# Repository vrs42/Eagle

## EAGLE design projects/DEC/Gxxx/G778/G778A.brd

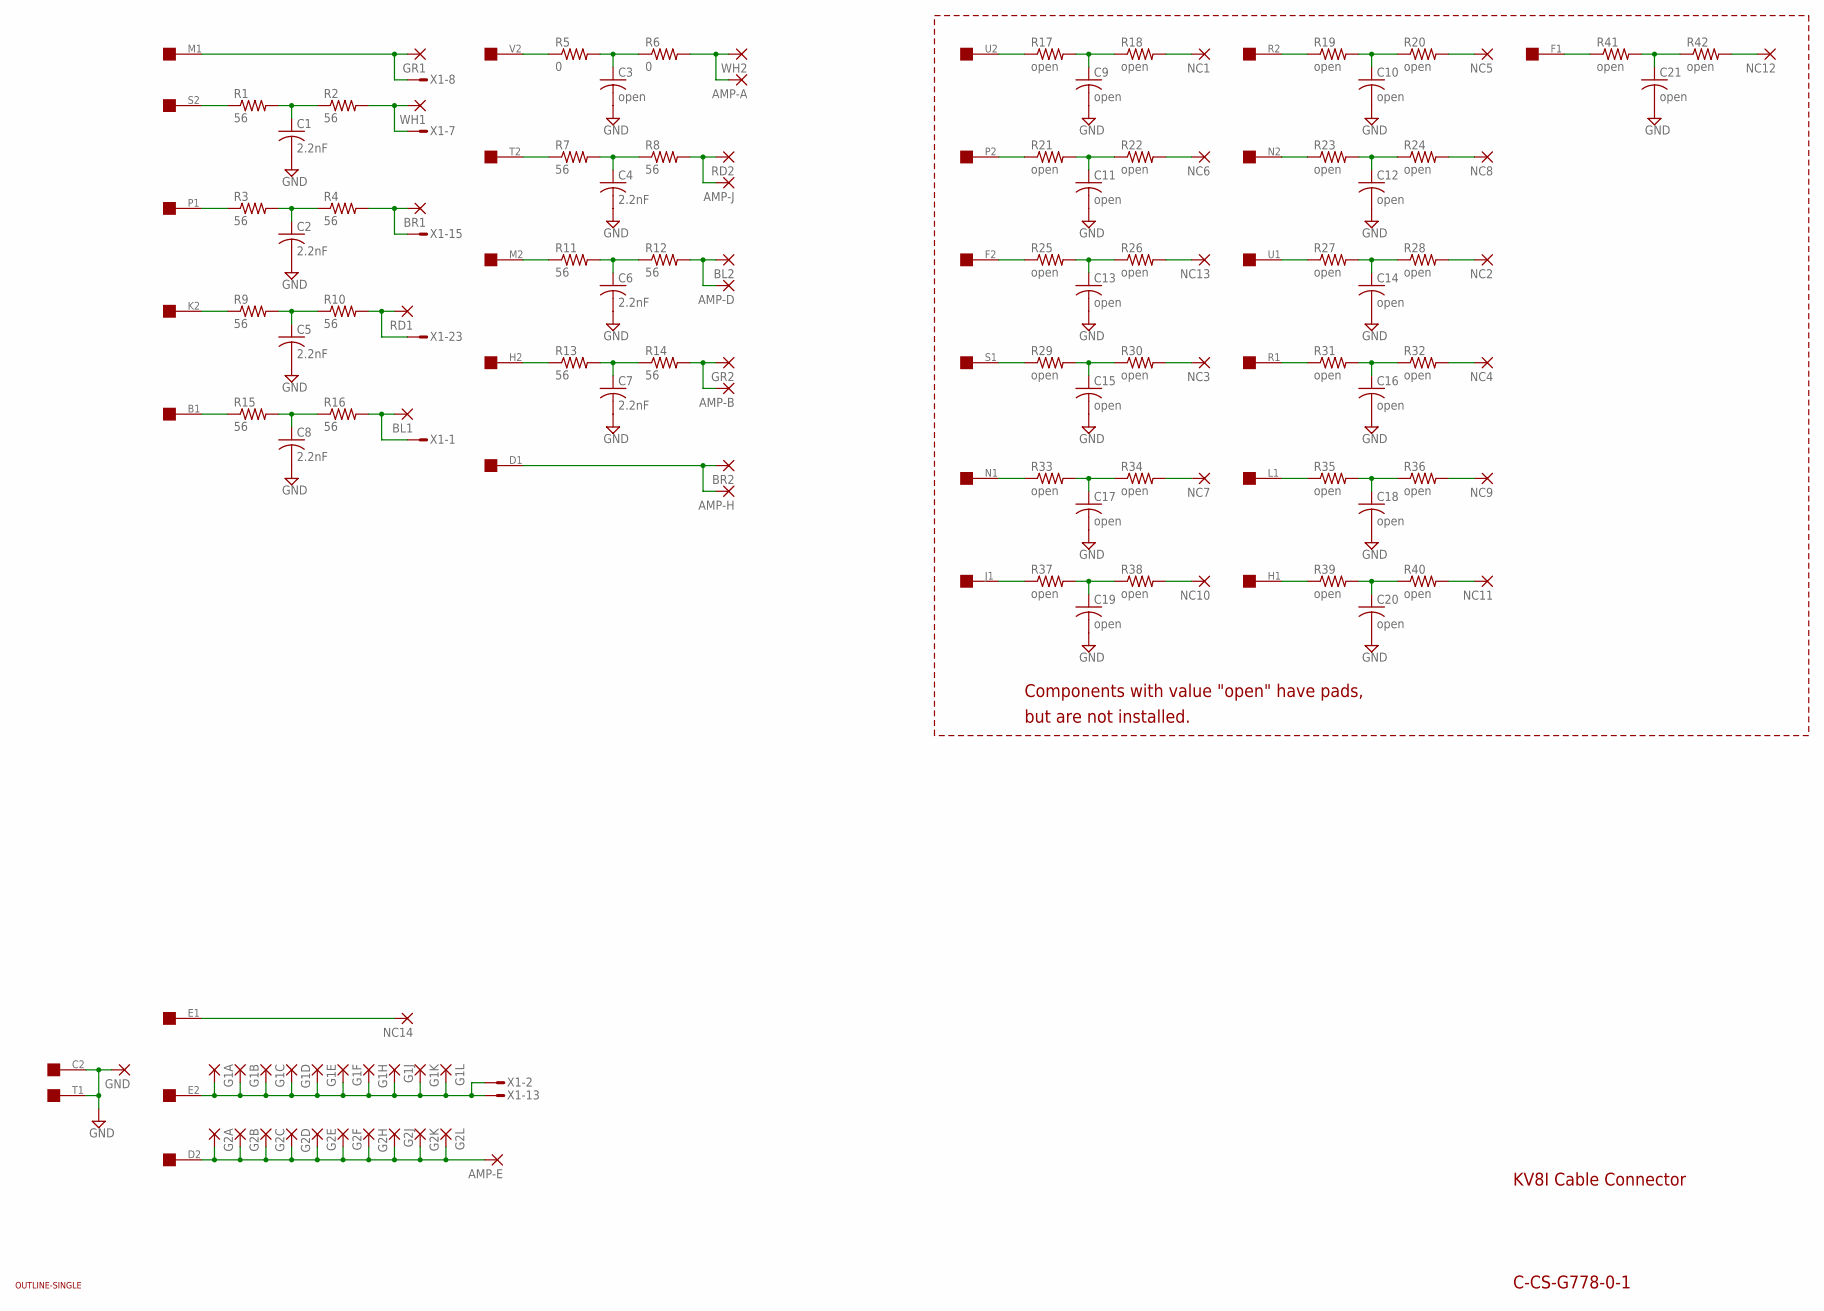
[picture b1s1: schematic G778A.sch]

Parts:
AMP-A: 2,54/1,0
AMP-B: 2,54/1,0
AMP-D: 2,54/1,0
AMP-E: 2,54/1,0
AMP-H: 2,54/1,0
AMP-J: 2,54/1,0
BL1, BL2: 2,54/1,0
BR1, BR2: 2,54/1,0
C1, C2, C4, C5, C6, C7, C8: 2.2nF; C102-043X133
C3, C9, C10, C11, C12, C13, C14, C15, C16, C17, C18, C19, C20, C21: open; C102-043X133
G1A, G1B, G1C, G1D, G1E, G1F, G1H, G1J, G1K, G1L, G2A, G2B, G2C, G2D, G2E, G2F, G2H, G2J, G2K, G2L: 2,54/1,0
GND: 2,54/1,0
GR1, GR2: 2,54/1,0
NC1, NC2, NC3, NC4, NC5, NC6, NC7, NC8, NC9, NC10, NC11, NC12, NC13, NC14: 2,54/1,0
R1, R2, R3, R4, R7, R8, R9, R10, R11, R12, R13, R14, R15, R16: 56; 0207/10
R5, R6: 0; 0207/10
R17, R18, R19, R20, R21, R22, R23, R24, R25, R26, R27, R28, R29, R30, R31, R32, R33, R34, R35, R36, R37, R38, R39, R40, R41, R42: open; 0207/10
RD1, RD2: 2,54/1,0
U$1: SINGLE; EDGE-CON2
U$2: OUTLINE-SINGLE; SINGLE
WH1, WH2: 2,54/1,0
X1: M25VS; M25V

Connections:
GND: C1.2, C2.2, C3.2, C4.2, C5.2, C6.2, C7.2, C8.2, C9.2, C10.2, C11.2, C12.2, C13.2, C14.2, C15.2, C16.2, C17.2, C18.2, C19.2, C20.2, C21.2, GND.1, U$1.C2, U$1.T1
unnamed: C1.1, R1.2, R2.1
unnamed: R1.1, U$1.S2
unnamed: R2.2, WH1.1, X1.7
unnamed: C2.1, R3.2, R4.1
unnamed: R3.1, U$1.P1
unnamed: BR1.1, R4.2, X1.15
unnamed: GR1.1, U$1.M1, X1.8
unnamed: G1A.1, G1B.1, G1C.1, G1D.1, G1E.1, G1F.1, G1H.1, G1J.1, G1K.1, G1L.1, U$1.E2, X1.2, X1.13
unnamed: AMP-E.1, G2A.1, G2B.1, G2C.1, G2D.1, G2E.1, G2F.1, G2H.1, G2J.1, G2K.1, G2L.1, U$1.D2
unnamed: C3.1, R5.2, R6.1
unnamed: R5.1, U$1.V2
unnamed: AMP-A.1, R6.2, WH2.1
unnamed: C4.1, R7.2, R8.1
unnamed: R7.1, U$1.T2
unnamed: AMP-J.1, R8.2, RD2.1
unnamed: C5.1, R9.2, R10.1
unnamed: R9.1, U$1.K2
unnamed: R10.2, RD1.1, X1.23
unnamed: C6.1, R11.2, R12.1
unnamed: R11.1, U$1.M2
unnamed: AMP-D.1, BL2.1, R12.2
unnamed: C7.1, R13.2, R14.1
unnamed: R13.1, U$1.H2
unnamed: AMP-B.1, GR2.1, R14.2
unnamed: C8.1, R15.2, R16.1
unnamed: R15.1, U$1.B1
unnamed: BL1.1, R16.2, X1.1
unnamed: C9.1, R17.2, R18.1
unnamed: R17.1, U$1.U2
unnamed: NC1.1, R18.2
unnamed: C10.1, R19.2, R20.1
unnamed: R19.1, U$1.R2
unnamed: NC5.1, R20.2
unnamed: C11.1, R21.2, R22.1
unnamed: R21.1, U$1.P2
unnamed: NC6.1, R22.2
unnamed: C12.1, R23.2, R24.1
unnamed: R23.1, U$1.N2
unnamed: NC8.1, R24.2
unnamed: C13.1, R25.2, R26.1
unnamed: R25.1, U$1.F2
unnamed: NC13.1, R26.2
unnamed: C14.1, R27.2, R28.1
unnamed: R27.1, U$1.U1
unnamed: NC2.1, R28.2
unnamed: C15.1, R29.2, R30.1
unnamed: R29.1, U$1.S1
unnamed: NC3.1, R30.2
unnamed: C16.1, R31.2, R32.1
unnamed: R31.1, U$1.R1
unnamed: NC4.1, R32.2
unnamed: C17.1, R33.2, R34.1
unnamed: R33.1, U$1.N1
unnamed: NC7.1, R34.2
unnamed: C18.1, R35.2, R36.1
unnamed: R35.1, U$1.L1
unnamed: NC9.1, R36.2
unnamed: C19.1, R37.2, R38.1
unnamed: R37.1, U$1.J1
unnamed: NC10.1, R38.2
unnamed: C20.1, R39.2, R40.1
unnamed: R39.1, U$1.H1
unnamed: NC11.1, R40.2
unnamed: C21.1, R41.2, R42.1
unnamed: R41.1, U$1.F1
unnamed: NC12.1, R42.2
unnamed: AMP-H.1, BR2.1, U$1.D1
unnamed: NC14.1, U$1.E1

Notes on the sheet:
KV8I Cable Connector
C-CS-G778-0-1
Components with value "open" have pads,
but are not installed.

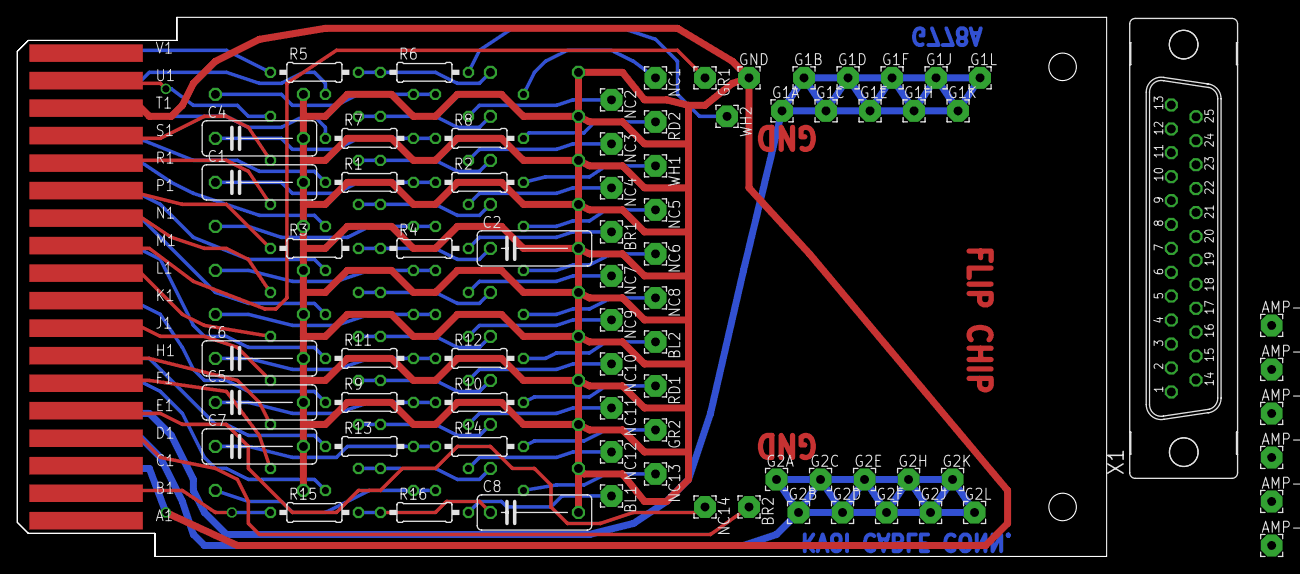
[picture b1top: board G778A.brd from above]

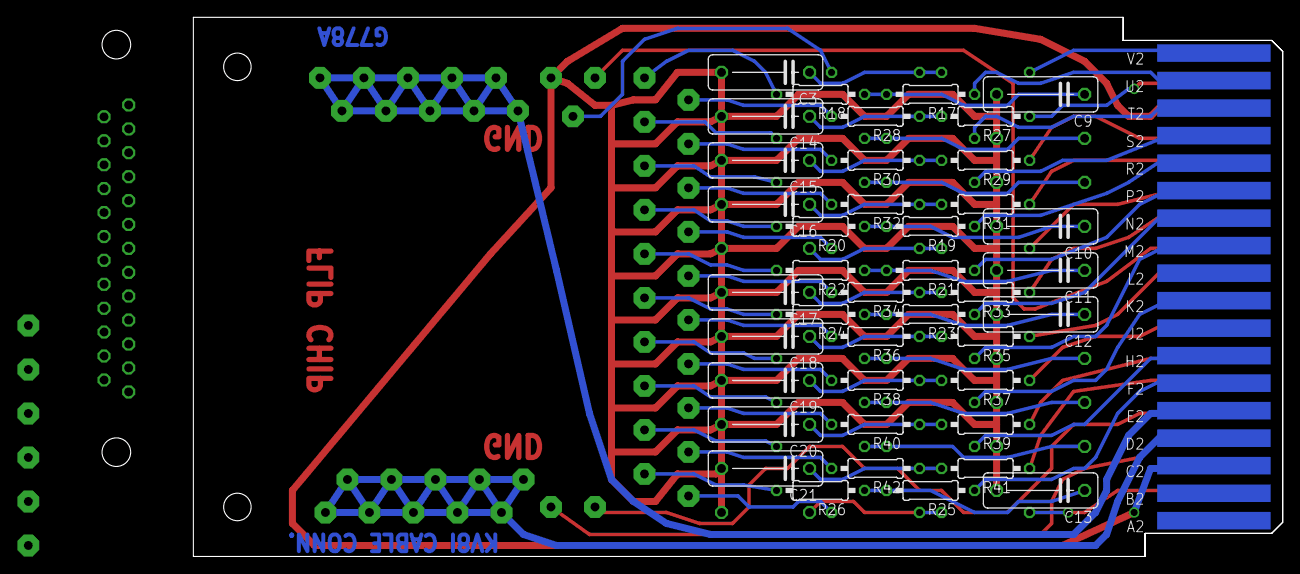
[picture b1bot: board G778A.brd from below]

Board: 2 copper layers, 125.7 x 62.2 mm, 117 parts (40 on the bottom side), 69 nets.

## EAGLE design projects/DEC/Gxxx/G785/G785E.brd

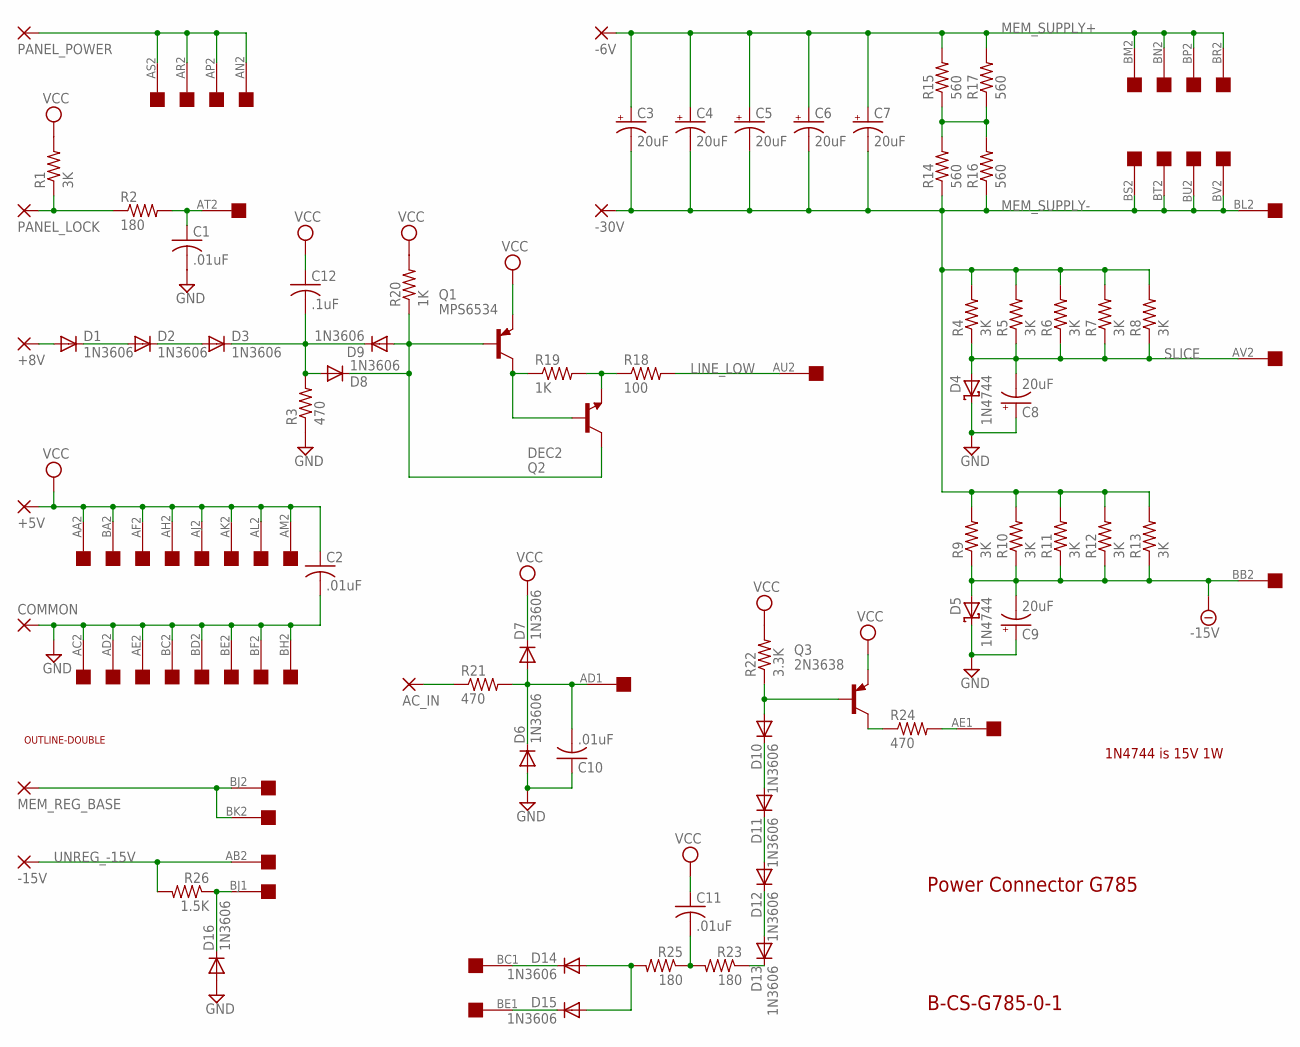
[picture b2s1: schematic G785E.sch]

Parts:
+5V, +8V: 3,81/1,4
-6V, -15V, -30V: 3,81/1,4
AC_IN: 3,81/1,4
C1, C2, C10, C11: .01uF; C050-025X075
C3, C4, C5, C6, C7, C8, C9: 20uF; E25-9
C12: .1uF; C102-043X133
COMMON: 3,81/1,4
D1, D2, D3, D6, D7, D8, D9, D10, D11, D12, D13, D14, D15, D16: 1N3606; DO35-10
D4, D5: 1N4744; DO35-10
MEM_REG_BASE: 3,81/1,4
PANEL_LOCK: 3,81/1,4
PANEL_POWER: 3,81/1,4
Q1: MPS6534; TO39
Q2: DEC2; TO5
Q3: 2N3638; TO39
R1, R4, R5, R6, R7, R8, R9, R10, R11, R12, R13: 3K; 0207/10
R2, R23, R25: 180; 0207/10
R3, R21, R24: 470; 0207/10
R14, R15, R16, R17: 560; 0207/10
R18: 100; 0207/10
R19, R20: 1K; 0207/10
R22: 3.3K; 0207/10
R26: 1.5K; 0207/10
U$1: DOUBLE; EDGE-CON4
U$2: OUTLINE-DOUBLE; DOUBLE

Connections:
-15V: C9.-, D5.A, R9.1, R10.1, R11.1, R12.1, R13.1, U$1.BB2
GND: C1.2, C2.2, C8.+, C9.+, C10.1, COMMON.1, D4.C, D5.C, D6.A, D16.A, R3.1, U$1.AC2, U$1.AD2, U$1.AE2, U$1.BC2, U$1.BD2, U$1.BE2, U$1.BF2, U$1.BH2
LINE_LOW: R18.2, U$1.AU2
MEM_SUPPLY+: -6V.1, C3.+, C4.+, C5.+, C6.+, C7.+, R15.2, R17.2, U$1.BM2, U$1.BN2, U$1.BP2, U$1.BR2
MEM_SUPPLY-: -30V.1, C3.-, C4.-, C5.-, C6.-, C7.-, R4.2, R5.2, R6.2, R7.2, R8.2, R9.2, R10.2, R11.2, R12.2, R13.2, R14.1, R16.1, U$1.BL2, U$1.BS2, U$1.BT2, U$1.BU2, U$1.BV2
unnamed: PANEL_LOCK.1, R1.1, R2.1
unnamed: C1.1, R2.2, U$1.AT2
unnamed: +8V.1, D1.A
unnamed: D1.C, D2.A
unnamed: D2.C, D3.A
unnamed: D8.C, D9.A, Q1.2 (B), Q2.3 (C), R20.1
unnamed: D14.C, U$1.BC1
unnamed: Q1.3 (C), Q2.2 (B), R19.1
unnamed: Q2.1 (E), R18.1, R19.2
unnamed: MEM_REG_BASE.1, U$1.BJ2, U$1.BK2
unnamed: R14.2, R15.1, R16.2, R17.1
unnamed: AC_IN.1, R21.1
unnamed: C10.2, D6.C, D7.A, R21.2, U$1.AD1
unnamed: D10.A, Q3.2 (B), R22.1
unnamed: Q3.3 (C), R24.1
unnamed: C11.2, R23.2, R25.1
unnamed: D14.A, D15.A, R25.2
unnamed: C12.2, D3.C, D8.A, D9.C, R3.2
unnamed: D13.C, R23.1
unnamed: D16.C, R26.1, U$1.BJ1
unnamed: D15.C, U$1.BE1
unnamed: D10.C, D11.A
unnamed: R24.2, U$1.AE1
unnamed: D11.C, D12.A
unnamed: D12.C, D13.A
PANEL_POWER: PANEL_POWER.1, U$1.AN2, U$1.AP2, U$1.AR2, U$1.AS2
SLICE: C8.-, D4.A, R4.1, R5.1, R6.1, R7.1, R8.1, U$1.AV2
UNREG_-15V: -15V.1, R26.2, U$1.AB2
VCC: +5V.1, C2.1, C11.1, C12.1, D7.C, Q1.1 (E), Q3.1 (E), R1.2, R20.2, R22.2, U$1.AA2, U$1.AF2, U$1.AH2, U$1.AJ2, U$1.AK2, U$1.AL2, U$1.AM2, U$1.BA2

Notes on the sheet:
Power Connector G785
B-CS-G785-0-1
1N4744 is 15V 1W

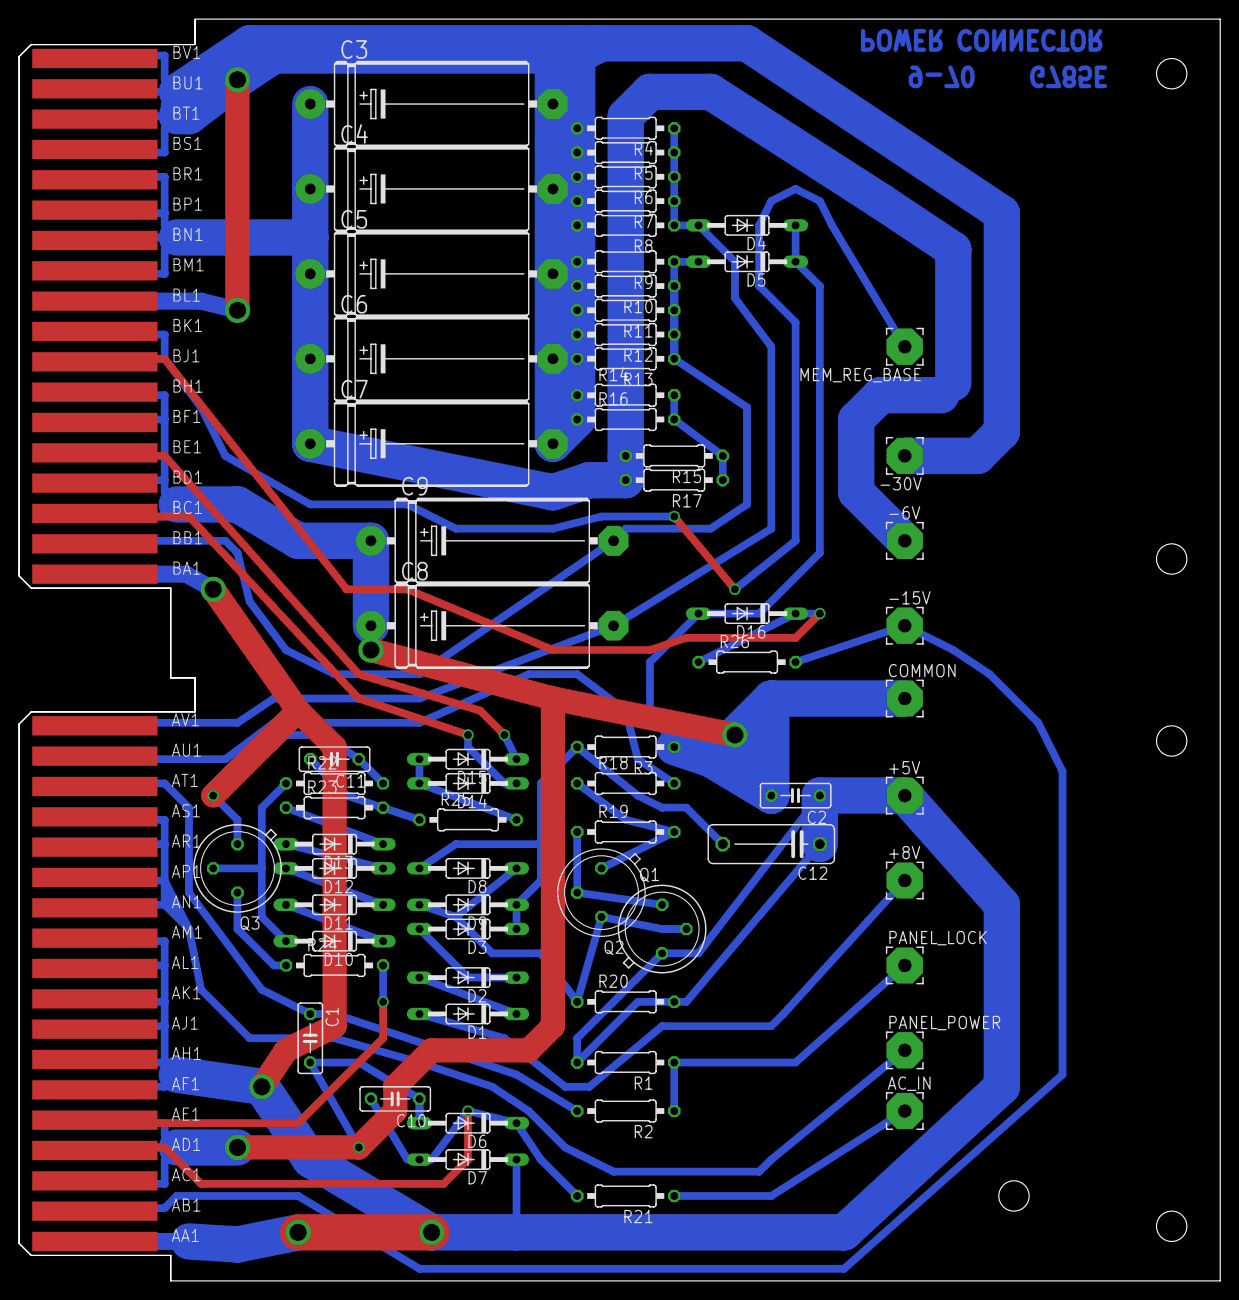
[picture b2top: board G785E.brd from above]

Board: 2 copper layers, 125.7 x 132.1 mm, 69 parts (0 on the bottom side), 34 nets.

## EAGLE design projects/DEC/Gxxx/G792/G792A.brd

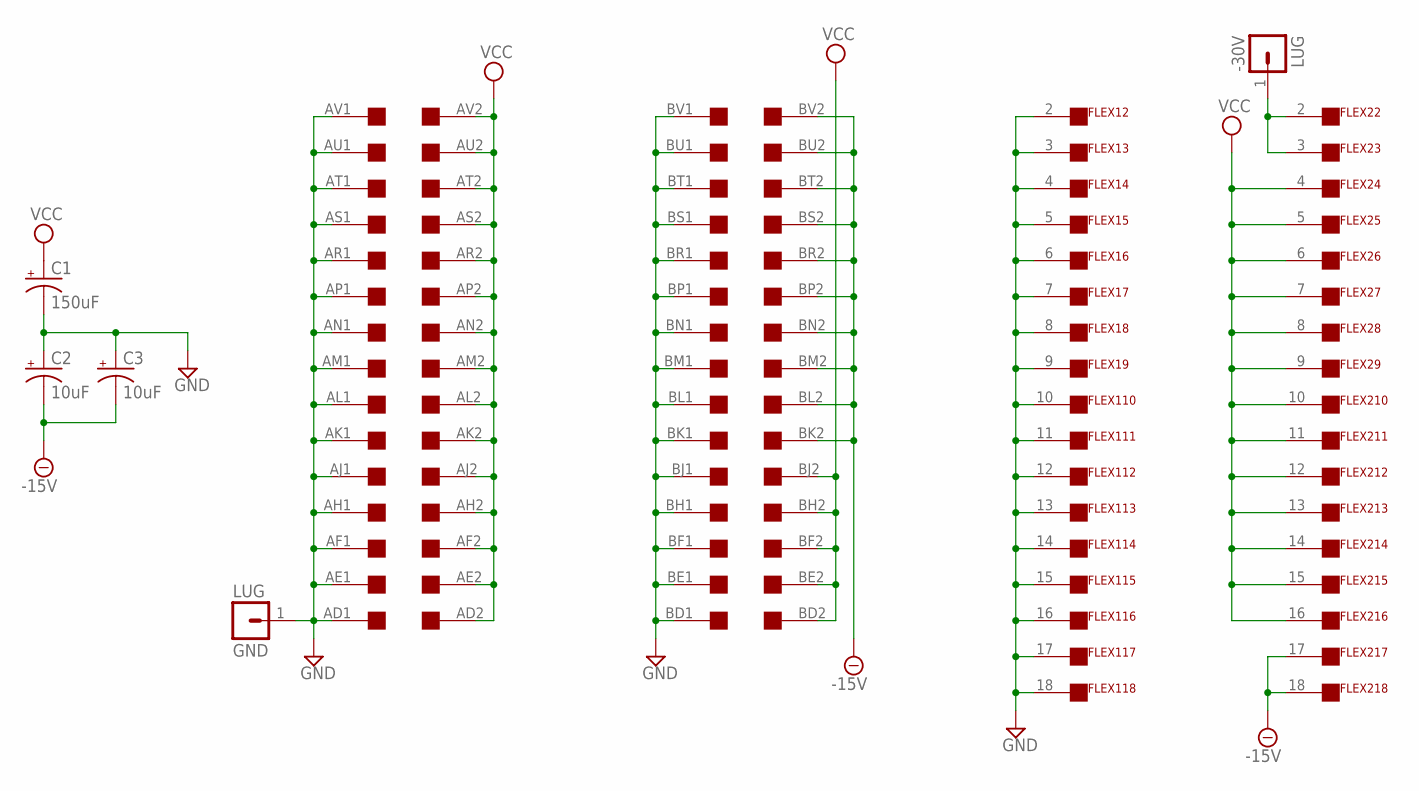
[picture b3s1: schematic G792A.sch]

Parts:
-30V: LUG; SPADELUG
C1: 150uF; E25-9
C2, C3: 10uF; E25-9
FLEX1, FLEX2: FLEX19W
GND: LUG; SPADELUG
U$2: DOUBLE; EDGE-CON4

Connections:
-15V: C2.-, C3.-, FLEX2.17, FLEX2.18, U$2.BK2, U$2.BL2, U$2.BM2, U$2.BN2, U$2.BP2, U$2.BR2, U$2.BS2, U$2.BT2, U$2.BU2, U$2.BV2
-30V: -30V.1, FLEX2.2, FLEX2.3
GND: C1.-, C2.+, C3.+, FLEX1.2, FLEX1.3, FLEX1.4, FLEX1.5, FLEX1.6, FLEX1.7, FLEX1.8, FLEX1.9, FLEX1.10, FLEX1.11, FLEX1.12, FLEX1.13, FLEX1.14, FLEX1.15, FLEX1.16, FLEX1.17, FLEX1.18, GND.1, U$2.AD1, U$2.AE1, U$2.AF1, U$2.AH1, U$2.AJ1, U$2.AK1, U$2.AL1, U$2.AM1, U$2.AN1, U$2.AP1, U$2.AR1, U$2.AS1, U$2.AT1, U$2.AU1, U$2.AV1, U$2.BD1, U$2.BE1, U$2.BF1, U$2.BH1, U$2.BJ1, U$2.BK1, U$2.BL1, U$2.BM1, U$2.BN1, U$2.BP1, U$2.BR1, U$2.BS1, U$2.BT1, U$2.BU1, U$2.BV1
VCC: C1.+, FLEX2.4, FLEX2.5, FLEX2.6, FLEX2.7, FLEX2.8, FLEX2.9, FLEX2.10, FLEX2.11, FLEX2.12, FLEX2.13, FLEX2.14, FLEX2.15, FLEX2.16, U$2.AD2, U$2.AE2, U$2.AF2, U$2.AH2, U$2.AJ2, U$2.AK2, U$2.AL2, U$2.AM2, U$2.AN2, U$2.AP2, U$2.AR2, U$2.AS2, U$2.AT2, U$2.AU2, U$2.AV2, U$2.BD2, U$2.BE2, U$2.BF2, U$2.BH2, U$2.BJ2

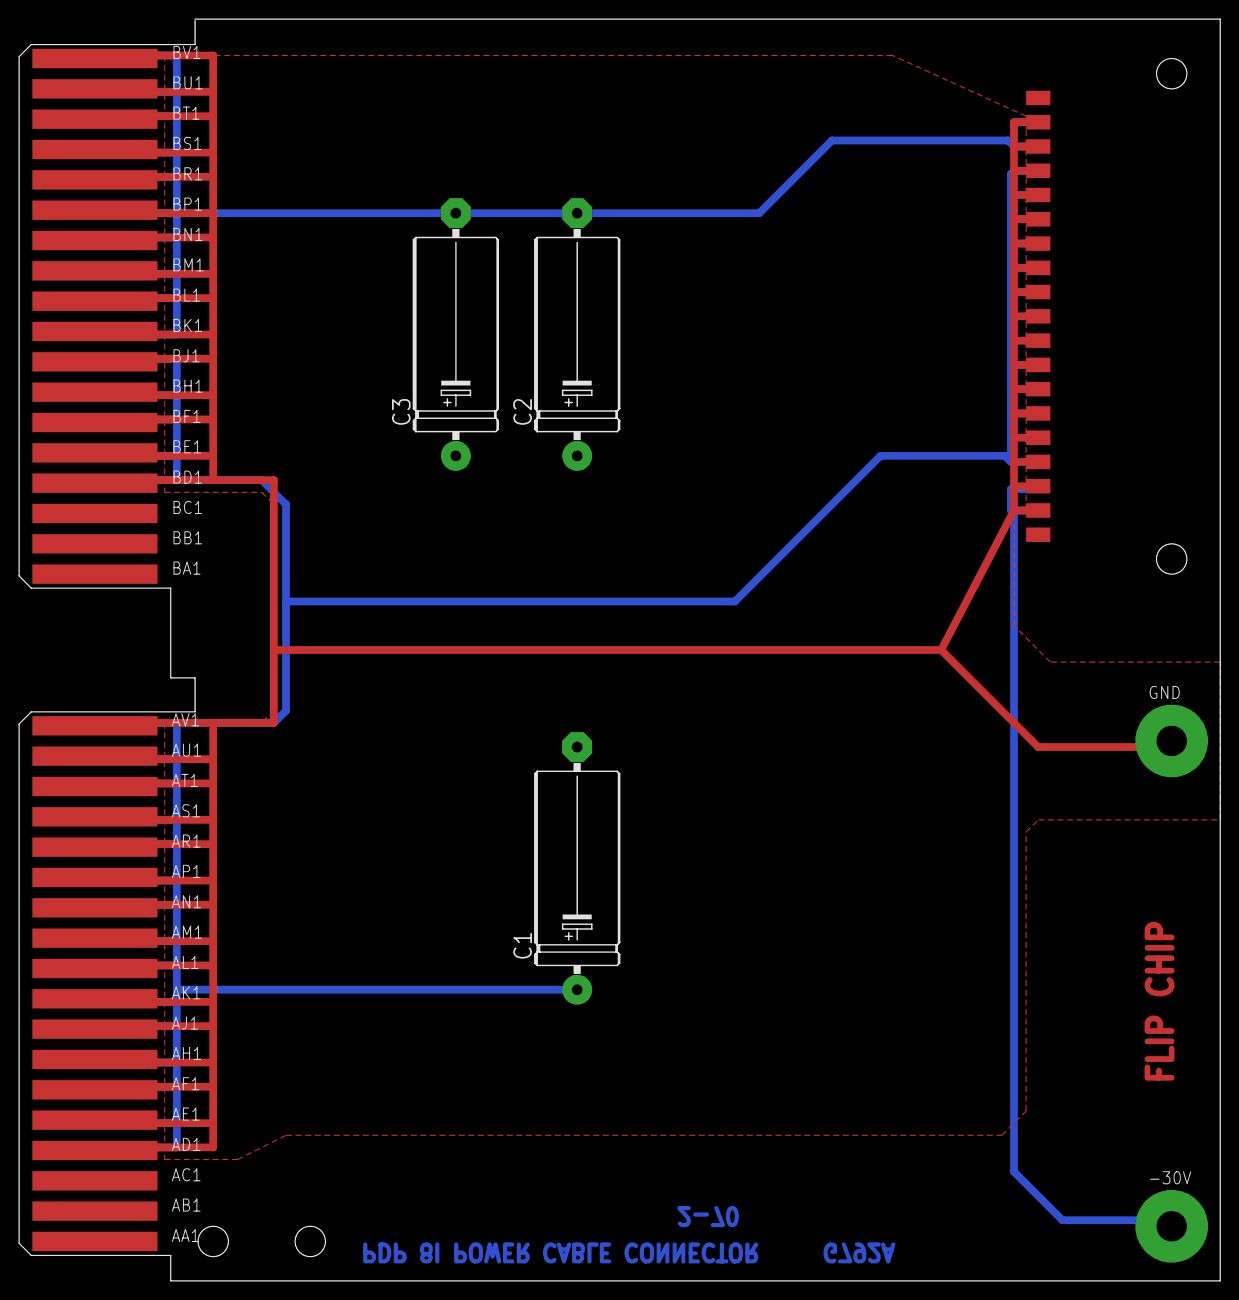
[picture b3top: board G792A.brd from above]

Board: 2 copper layers, 125.7 x 132.1 mm, 9 parts (1 on the bottom side), 4 nets.

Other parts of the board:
U$3: FLIPCHIP

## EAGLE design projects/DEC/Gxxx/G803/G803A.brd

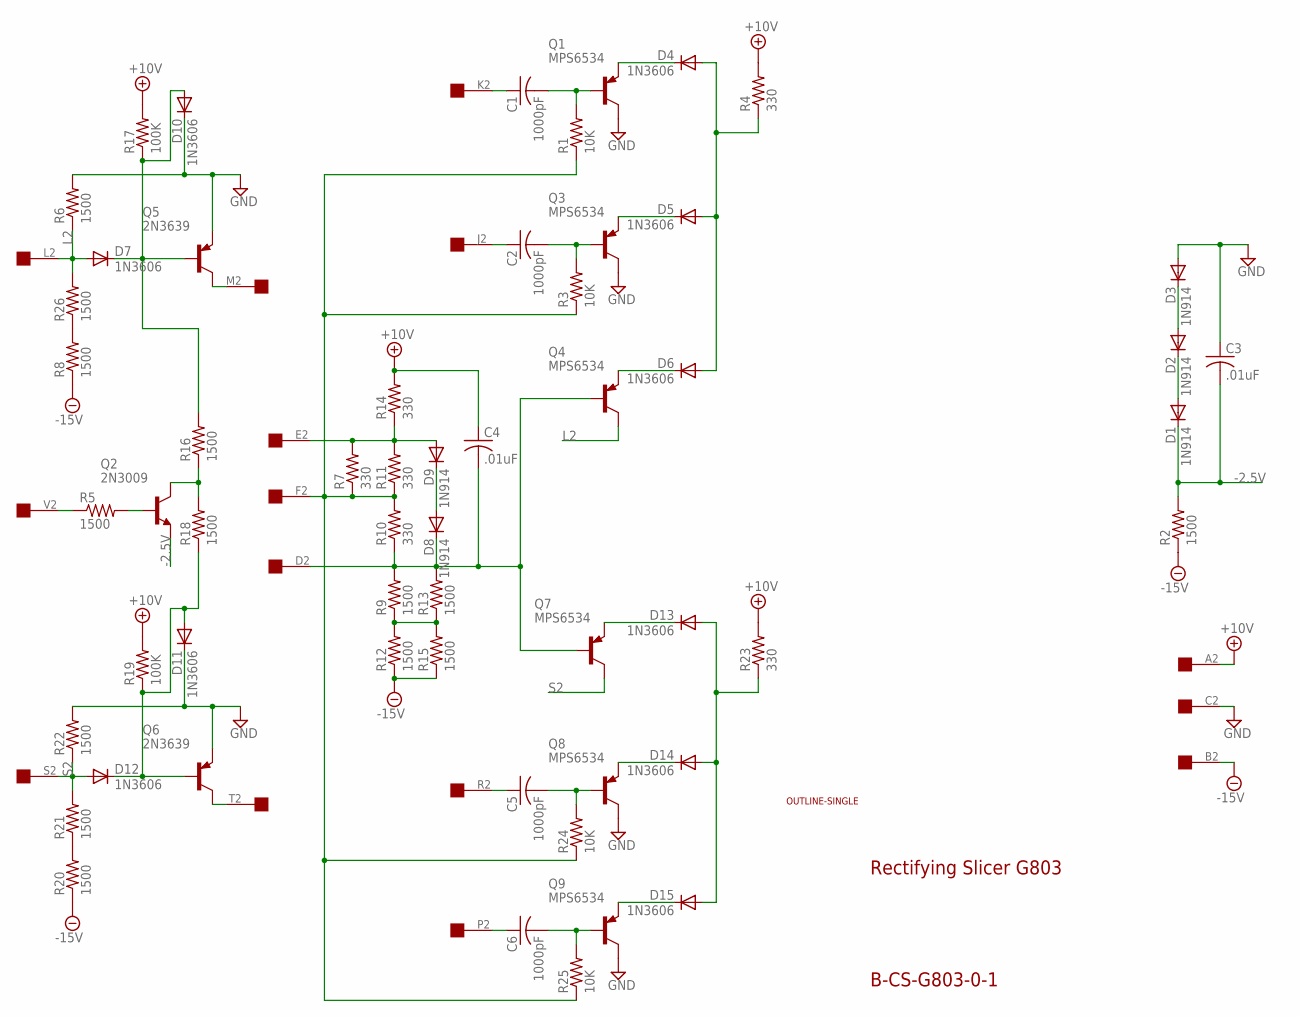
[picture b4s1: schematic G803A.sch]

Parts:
C1, C2, C5, C6: 1000pF; C075-032X103
C3: .01uF; C050-025X075
C4: .01uF; C075-032X103
D1, D2, D3, D8, D9: 1N914; DO35-10
D4, D5, D6, D7, D10, D11, D12, D13, D14, D15: 1N3606; DO35-10
Q1, Q3, Q4, Q7, Q8, Q9: MPS6534; TO39
Q2: 2N3009; TO5
Q5, Q6: 2N3639; TO39
R1, R3, R24, R25: 10K; 0207/10
R2, R5, R6, R8, R9, R12, R13, R15, R16, R18, R20, R21, R22, R26: 1500; 0207/10
R4, R7, R10, R11, R14, R23: 330; 0207/10
R17, R19: 100K; 0207/10
U$1: OUTLINE-SINGLE; SINGLE
U$2: EDGE-1; EDGE-CON1

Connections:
+10V: C4.1, R4.2, R14.2, R17.2, R19.2, R23.2, U$2.A2
-2.5V: C3.2, D1.C, Q2.1 (E), R2.2
-15V: R2.1, R8.1, R12.1, R15.1, R20.1, U$2.B2
GND: C3.1, D3.A, D10.C, D11.C, Q1.3 (C), Q3.3 (C), Q5.1 (E), Q6.1 (E), Q8.3 (C), Q9.3 (C), R6.2, R22.2, U$2.C2
L2: D7.A, Q4.3 (C), R6.1, R26.2, U$2.L2
unnamed: C1.1, U$2.K2
unnamed: R5.1, U$2.V2
unnamed: C1.2, Q1.2 (B), R1.2
unnamed: D4.C, Q1.1 (E)
unnamed: D5.C, Q3.1 (E)
unnamed: C2.1, U$2.J2
unnamed: D14.C, Q8.1 (E)
unnamed: C2.2, Q3.2 (B), R3.2
unnamed: D15.C, Q9.1 (E)
unnamed: Q2.2 (B), R5.2
unnamed: C5.1, U$2.R2
unnamed: Q6.3 (C), U$2.T2
unnamed: C5.2, Q8.2 (B), R24.2
unnamed: Q5.3 (C), U$2.M2
unnamed: R8.2, R26.1
unnamed: C6.1, U$2.P2
unnamed: D13.C, Q7.1 (E)
unnamed: C6.2, Q9.2 (B), R25.2
unnamed: R20.2, R21.1
unnamed: D6.C, Q4.1 (E)
unnamed: D7.C, D10.A, Q5.2 (B), R16.2, R17.1
unnamed: Q2.3 (C), R16.1, R18.2
unnamed: C4.2, D8.C, Q4.2 (B), Q7.2 (B), R9.2, R10.1, R13.2, U$2.D2
unnamed: D11.A, D12.C, Q6.2 (B), R18.1, R19.1
unnamed: R9.1, R12.2, R13.1, R15.2
unnamed: R1.1, R3.1, R7.1, R10.2, R11.1, R24.1, R25.1, U$2.F2
unnamed: D2.A, D3.C
unnamed: D4.A, D5.A, D6.A, R4.1
unnamed: D1.A, D2.C
unnamed: D8.A, D9.C
unnamed: D9.A, R7.2, R11.2, R14.1, U$2.E2
unnamed: D13.A, D14.A, D15.A, R23.1
S2: D12.A, Q7.3 (C), R21.2, R22.1, U$2.S2

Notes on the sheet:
Rectifying Slicer G803
B-CS-G803-0-1

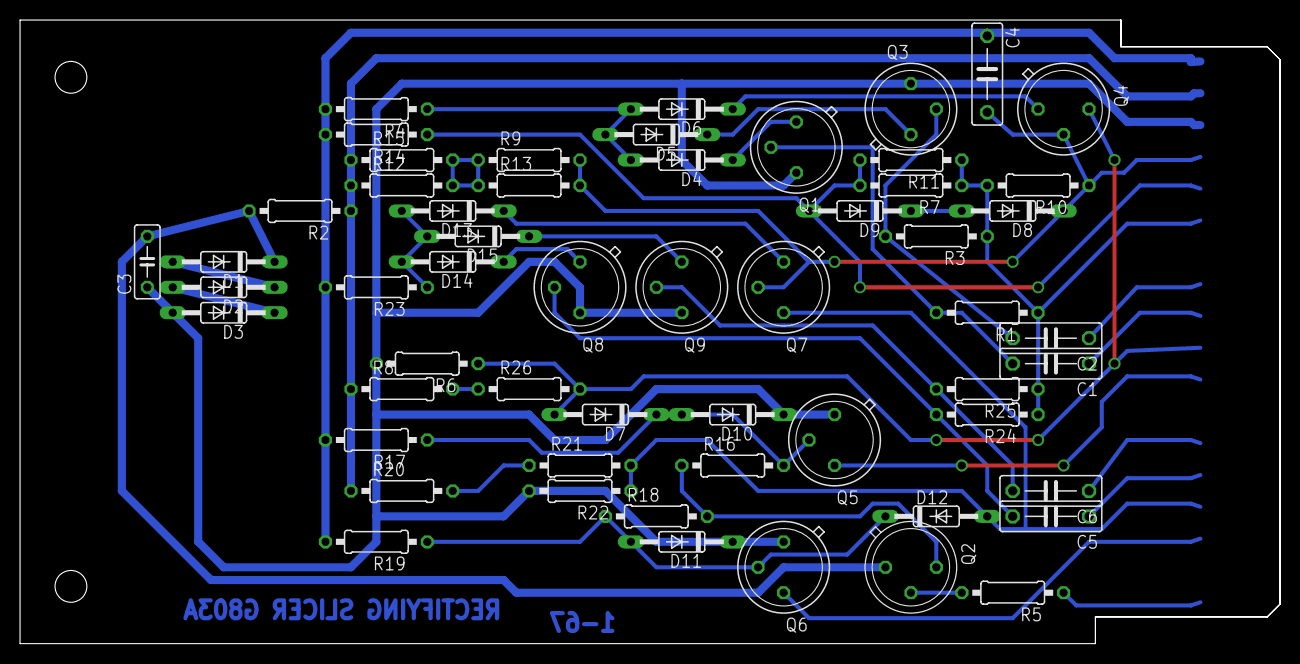
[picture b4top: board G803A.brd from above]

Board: 2 copper layers, 125.7 x 62.2 mm, 58 parts (0 on the bottom side), 38 nets.

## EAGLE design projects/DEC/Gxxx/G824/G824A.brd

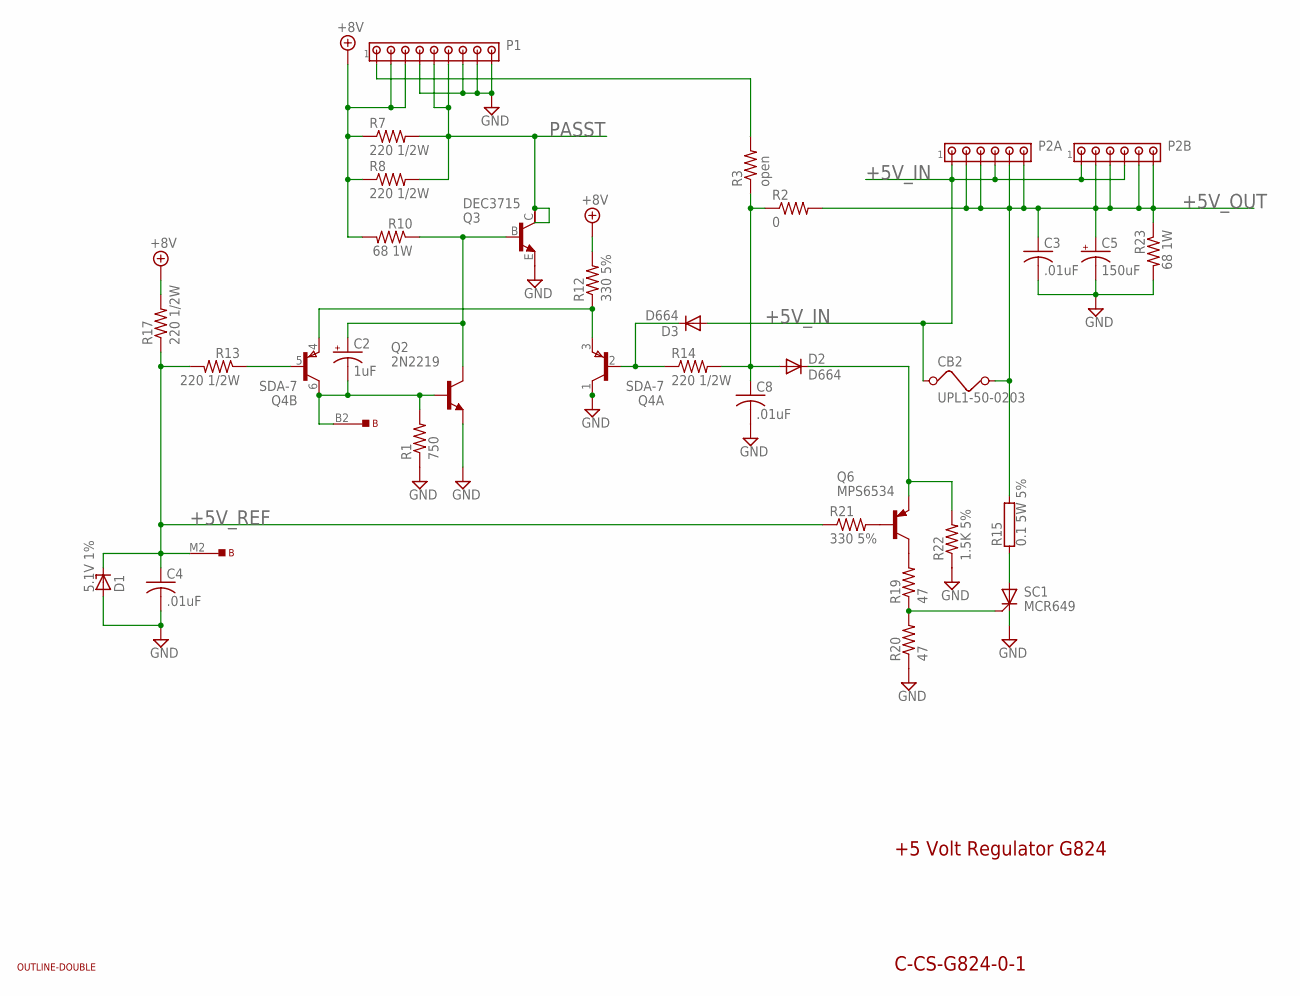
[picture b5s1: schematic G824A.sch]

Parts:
B: EDGE-TOP; EDGE-CON2
C2: 1uF; E15-5
C3, C4, C8: .01uF; C063-025X075
C5: 150uF; E12-8
CB2: UPL1-50-0203; UPL1-50
D1: 5.1V 1%; DO41Z10
D2, D3: D664; DO35-10
P1: 350432-1
P2A, P2B: 350431-1
Q2: 2N2219; TO5
Q3: DEC3715; TO3
Q4: SDA-7; TO78
Q6: MPS6534; TO5
R1: 750; 0207/10
R2: 0; 0207/10
R3: open; 0207/10
R7, R8, R13, R14, R17: 220 1/2W; 0411/15
R10, R23: 68 1W; 0414/20
R12, R21: 330 5%; 0207/10
R15: 0.1 5W 5%; HPS932
R19, R20: 47; 0207/10
R22: 1.5K 5%; 0207/10
SC1: MCR649; TO3A
U$1: OUTLINE-DOUBLE; DOUBLE

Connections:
+5V_IN: CB2.1, D3.A, P2A.1, P2A.4, P2B.1, P2B.4
+5V_OUT: C3.1, C5.+, CB2.2, P2A.2, P2A.3, P2A.5, P2A.6, P2B.2, P2B.3, P2B.5, P2B.6, R2.2, R15.2, R23.1
+5V_REF: B.M2, C4.1, D1.C, R13.2, R17.1, R21.1
+8V: P1.2, P1.3, R7.1, R8.1, R10.2, R12.2, R17.2
GND: C3.2, C4.2, C5.-, C8.2, D1.A, P1.4, P1.7, P1.8, P1.9, Q2.1 (E), Q3.E, Q4.1 (C), R1.1, R20.1, R22.1, R23.2, SC1.1 (C)
unnamed: Q4.5 (B), R13.1
unnamed: Q4.3 (E), Q4.4 (E), R12.1
unnamed: B.B2, C2.-, Q2.2 (B), Q4.6 (C), R1.2
unnamed: P1.1, R3.2
unnamed: D3.C, Q4.2 (B), R14.1
unnamed: C2.+, Q2.3 (C), Q3.B, R10.1
unnamed: Q6.2 (B), R21.2
unnamed: Q6.3 (C), R19.2
unnamed: R19.1, R20.2, SC1.2 (G)
unnamed: D2.C, Q6.1 (E), R22.2
unnamed: C8.1, D2.A, R2.1, R3.1, R14.2
unnamed: R15.1, SC1.3 (A)
PASST: P1.5, P1.6, Q3.C, Q3.C/ (C), R7.2, R8.2

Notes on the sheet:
+5 Volt Regulator G824
C-CS-G824-0-1

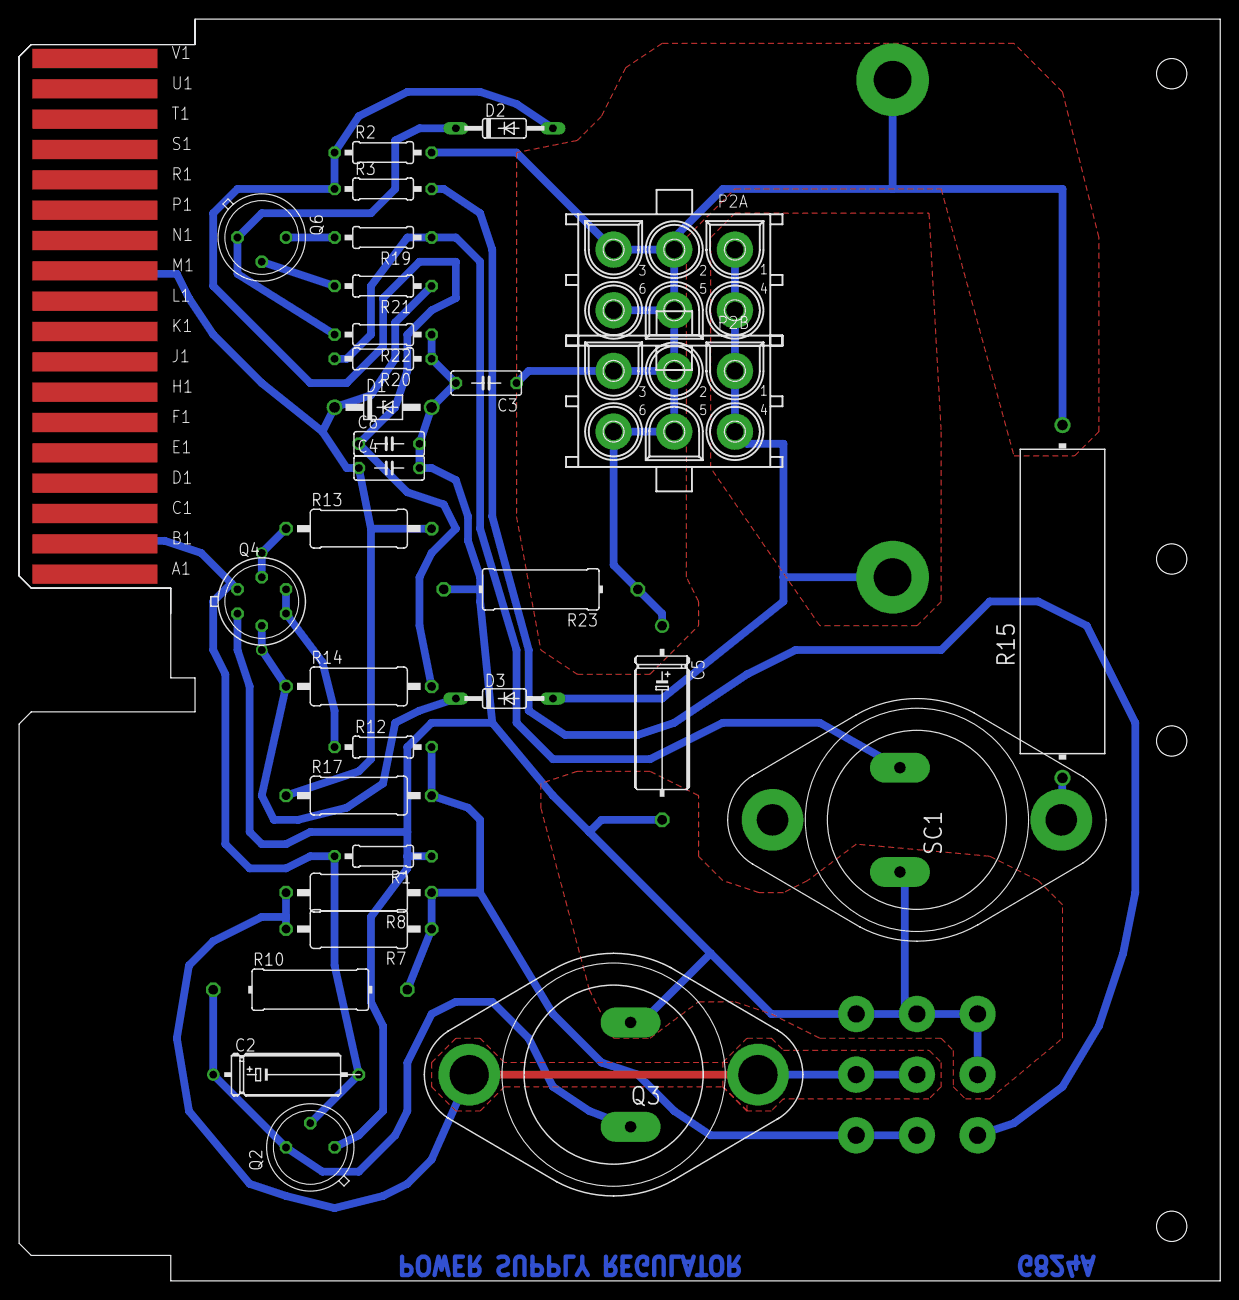
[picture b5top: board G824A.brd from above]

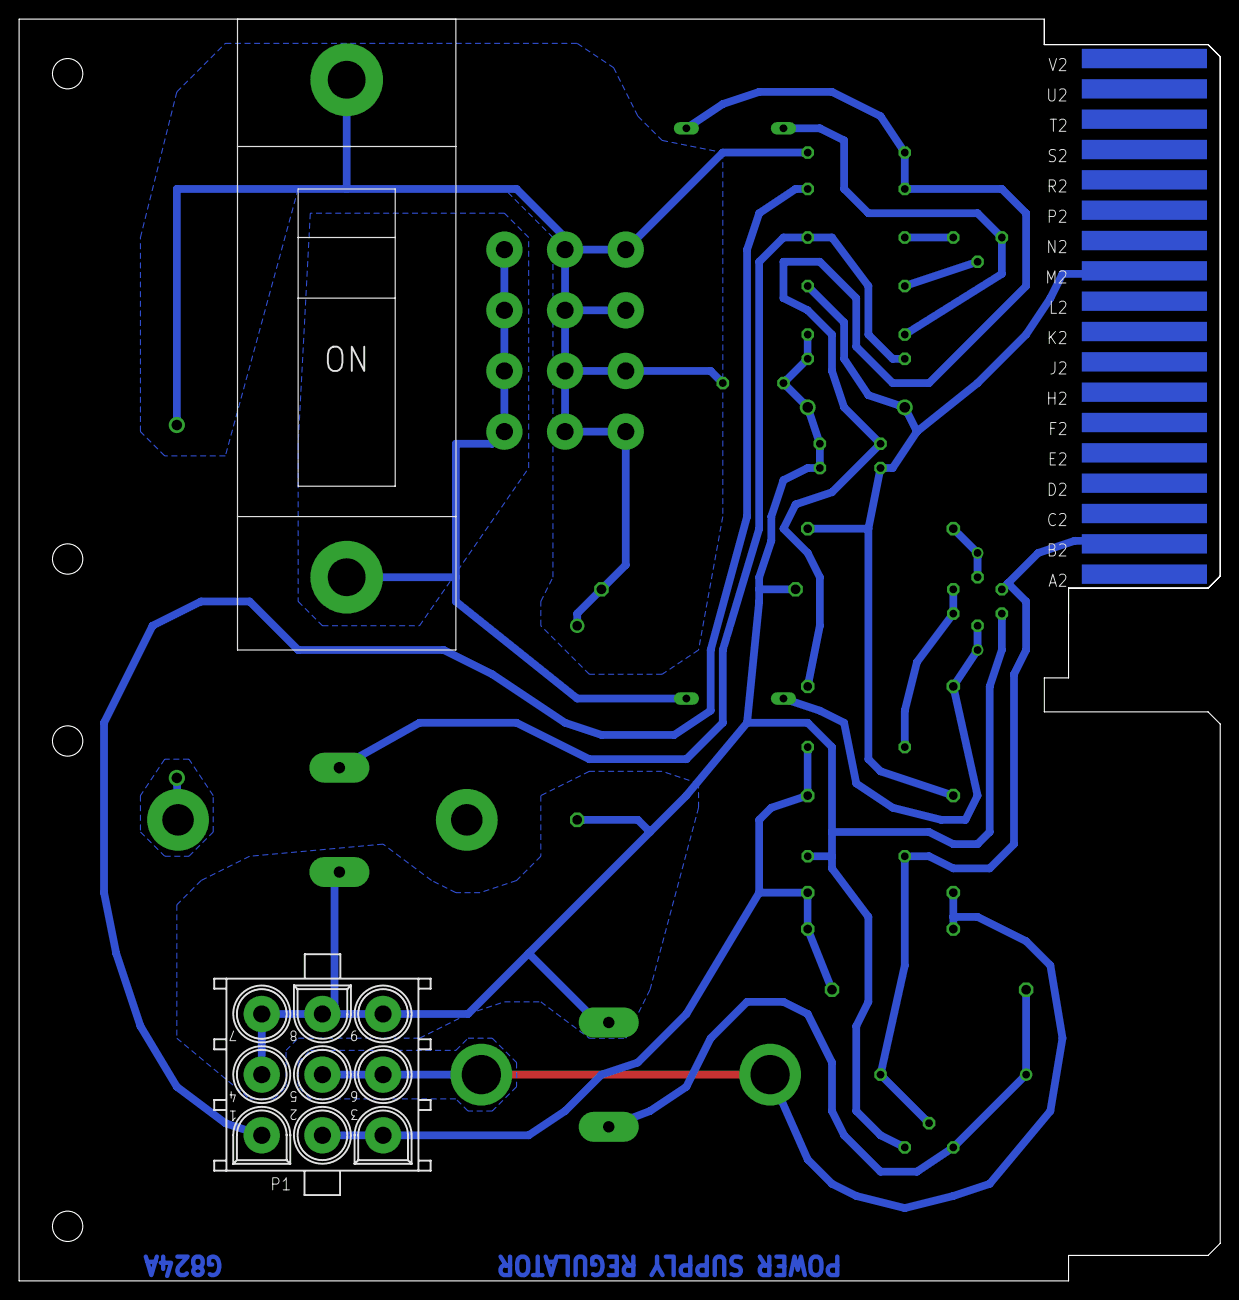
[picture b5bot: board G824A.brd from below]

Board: 2 copper layers, 125.7 x 132.1 mm, 35 parts (2 on the bottom side), 18 nets.
